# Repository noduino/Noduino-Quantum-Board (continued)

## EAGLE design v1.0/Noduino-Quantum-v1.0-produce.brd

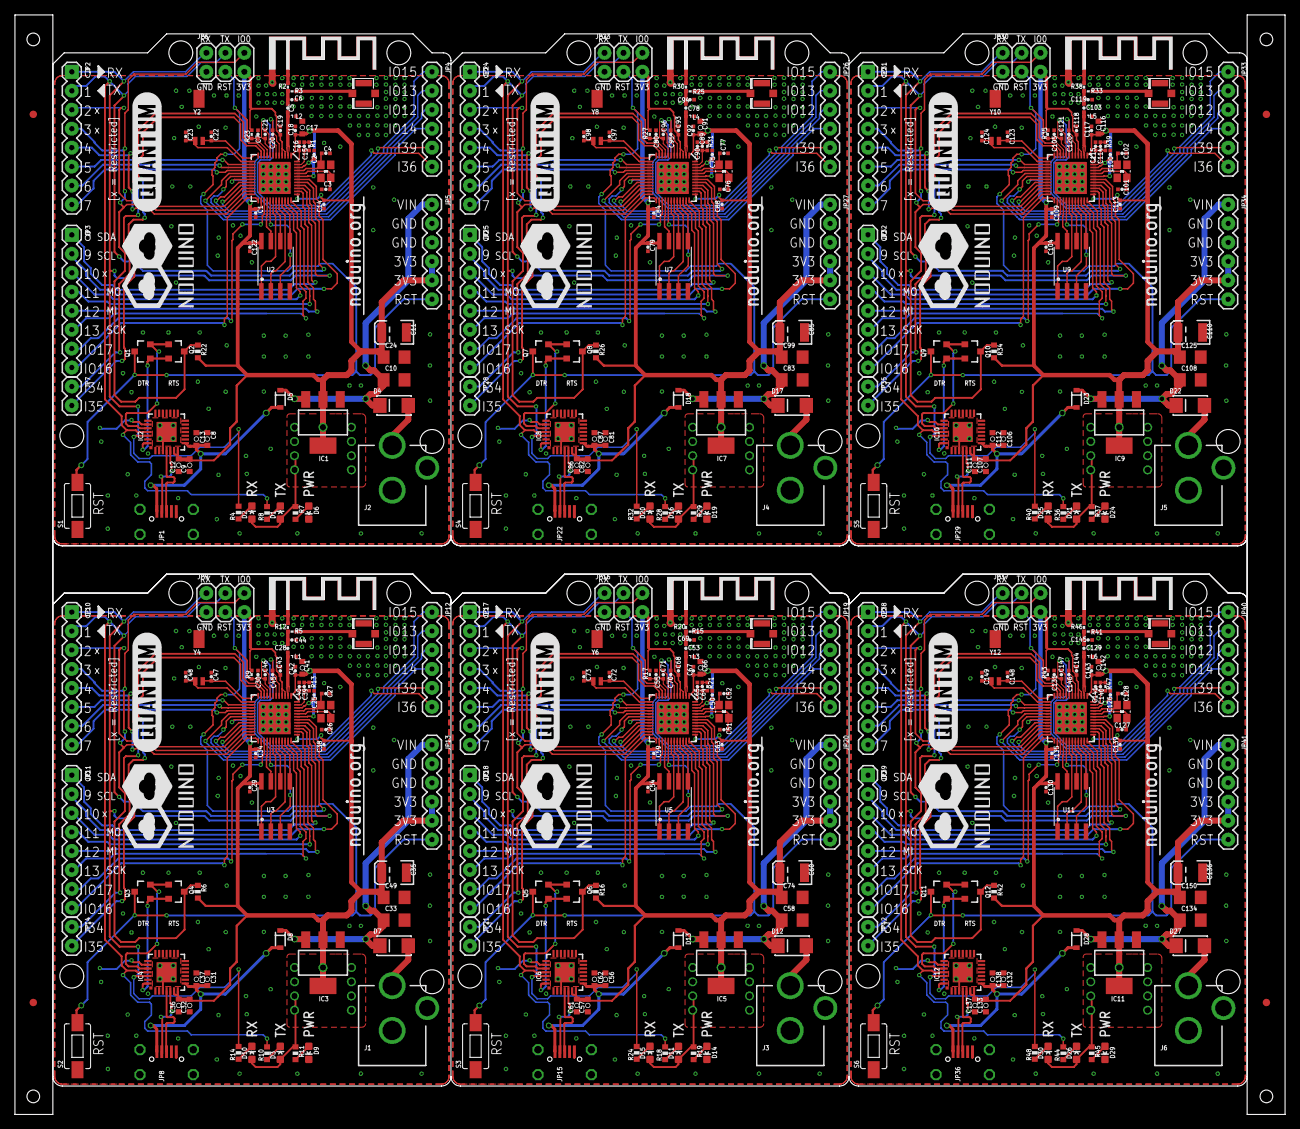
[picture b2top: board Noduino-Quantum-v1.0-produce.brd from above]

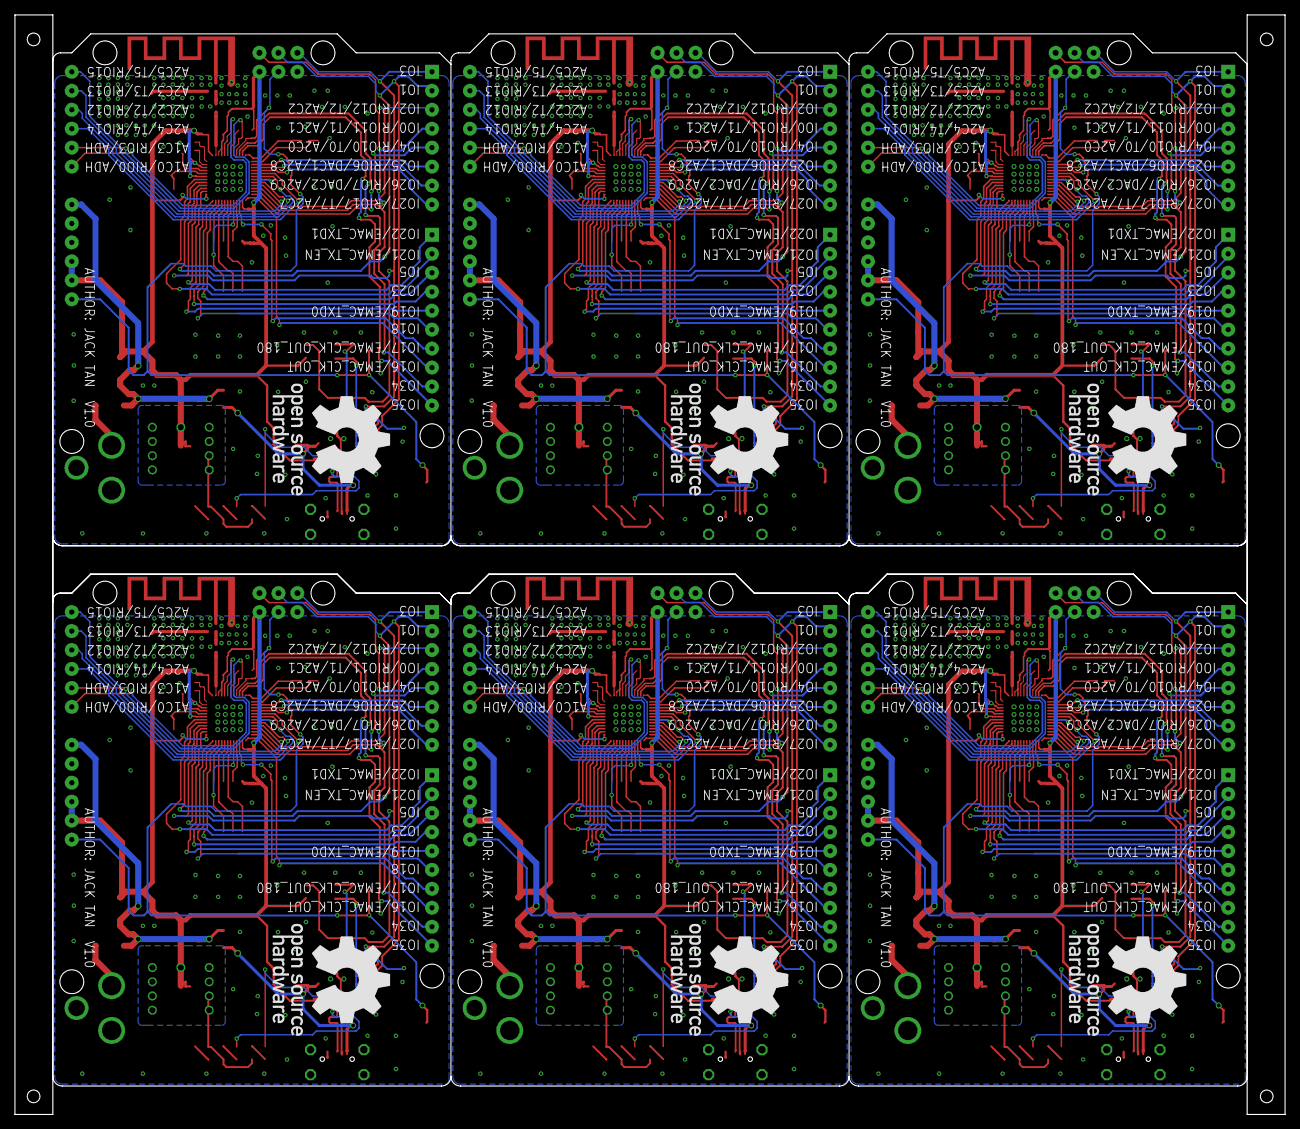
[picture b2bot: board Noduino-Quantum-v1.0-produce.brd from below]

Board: 2 copper layers, 170.2 x 147.3 mm, 370 parts (6 on the bottom side), 330 nets.

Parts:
A1, A4, A6, A8, A10, A12: TRACE_ANTENNA_2.4GHZ_15.2MM_TPLACE
A2, A3, A5, A7, A9, A11: U.FL
C1, C7, C14, C18, C19, C29, C30, C34, C38, C42, C43, C54, C55, C59, C63, C67, C68, C79, C80, C84, C88, C92, C93, C104, C105, C109, C113, C117, C118, C122, C130, C131, C135, C139, C143, C144: 100nF; 0402-CAP
C2, C25, C50, C75, C100, C126: 100pF; 0402-CAP
C3, C4, C26, C27, C51, C52, C76, C77, C101, C102, C127, C128: 15pF; 0402-CAP
C5, C28, C53, C78, C103, C129: 6.8pF; 0402-CAP
C6, C44, C69, C94, C119, C145: 2.4pF; 0402-CAP
C8, C9, C31, C32, C56, C57, C81, C82, C106, C107, C132, C133: 100nF; 0603-CAP
C10, C33, C58, C83, C108, C134: 22uF; C1206
C11, C35, C60, C85, C110, C136: 100uF; EIA3528
C12, C36, C61, C86, C111, C137: 4.7uF; 0603-CAP
C13, C37, C62, C87, C112, C138: 1uF; 0603-CAP
C15, C39, C64, C89, C114, C140: 3nF; 0402-CAP
C16, C40, C65, C90, C115, C141: 10nF; 0402-CAP
C17, C41, C66, C91, C116, C142: 10uF; 0603-CAP
C20, C21, C45, C46, C70, C71, C95, C96, C120, C121, C146, C147: 270pF; 0402-CAP
C22, C23, C47, C48, C72, C73, C97, C98, C123, C124, C148, C149: 12pF; 0402-CAP
C24, C49, C74, C99, C125, C150: 10uF; C1206
D1, D2, D3, D10, D11, D15, D16, D20, D21, D25, D26, D30: BLUE; LED-0603
D4, D7, D12, D17, D22, D27: SS4; DO214
D5, D8, D13, D18, D23, D28: S4; SOD-323
D6, D9, D14, D19, D24, D29: GREEN; LED-0603
E$1, E$2, E$3, E$4: MARK-1MM
IC1, IC3, IC5, IC7, IC9, IC11: 1117-3.3; SOT223
IC2, IC4, IC6, IC8, IC10, IC12: CP210X_USB_UART; MLP28
J1, J2, J3, J4, J5, J6: POWER_JACKPTH; POWER_JACK_PTH
JP1, JP8, JP15, JP22, JP29, JP36: MICROUSB-SMD-DIP
JP2, JP3, JP10, JP11, JP17, JP18, JP24, JP25, JP31, JP32, JP38, JP39: M081X08; 1X08
JP4, JP5, JP12, JP13, JP19, JP20, JP26, JP27, JP33, JP34, JP40, JP41: M06SIP; 1X06
JP6, JP9, JP16, JP23, JP30, JP37: M02X3; 2X3
JP7, JP14, JP21, JP28, JP35, JP42: 1X02
L1, L2, L3, L4, L5, L6: 1.6nH; 0402-IND
Q1, Q2, Q3, Q4, Q5, Q6, Q7, Q8, Q9, Q10, Q11, Q12: SI2302; SOT23-3
R1, R13, R21, R31, R39, R47: 20K; 0402-RES
R2, R12, R20, R30, R38, R46: 0R; 0402-RES
R3, R5, R15, R25, R33, R41: DNP; 0402-RES
R4, R7, R8, R10, R11, R14, R18, R19, R24, R28, R29, R32, R36, R37, R40, R44, R45, R48: 1K; 0603-RES
R6, R16, R22, R26, R34, R42: 10K; 0603-RES
R9, R17, R23, R27, R35, R43: 10K; 0402-RES
S1, S2, S3, S4, S5, S6: SWITCH-SMD; TACTILE-SWITCH-1101NE
U1, U4, U6, U8, U10, U12: ESP32; QFN48-0.4MM
U2, U3, U5, U7, U9, U11: SPI_FLASH-X25XXSMD1; SO08-EIAJ
U$1, U$4, U$7, U$10, U$13, U$16: NODUINO-LOGO-ALL; NODUINO-ALL-1
U$2, U$5, U$8, U$11, U$14, U$17: NODUINO-QUANTUM-LOGO
U$3, U$6, U$9, U$12, U$15, U$18: OPEN_HARDWARE_LOGO
Y1, Y3, Y5, Y7, Y9, Y11: 40MHz; 2520-CRY
Y2, Y4, Y6, Y8, Y10, Y12: 32KHz; CRYSTAL-32KHZ-MS3V

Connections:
3V1: C25.1, C29.1, C32.2, C34.1, C35.A, C36.2, C38.2, C41.1, C42.1, C43.2, C49.1, D3.A, D10.A, IC3.2, IC3.4, IC4.6, IC4.7, JP9.5, JP13.4, JP13.5, R6.2, R9.2, R11.1, U3.8, U4.1, U4.3, U4.4, U4.19, U4.26, U4.37, U4.43, U4.46
3V2: C50.1, C54.1, C57.2, C59.1, C60.A, C61.2, C63.2, C66.1, C67.1, C68.2, C74.1, D11.A, D15.A, IC5.2, IC5.4, IC6.6, IC6.7, JP16.5, JP20.4, JP20.5, R16.2, R17.2, R19.1, U5.8, U6.1, U6.3, U6.4, U6.19, U6.26, U6.37, U6.43, U6.46
3V3: C1.1, C2.1, C9.2, C11.A, C12.2, C14.2, C17.1, C18.1, C19.2, C24.1, C122.1, D1.A, D2.A, IC1.2, IC1.4, IC2.6, IC2.7, JP5.4, JP5.5, JP6.5, R7.1, R22.2, R23.2, U1.1, U1.3, U1.4, U1.19, U1.26, U1.37, U1.43, U1.46, U2.8
3V4: C75.1, C79.1, C82.2, C84.1, C85.A, C86.2, C88.2, C91.1, C92.1, C93.2, C99.1, D16.A, D20.A, IC7.2, IC7.4, IC8.6, IC8.7, JP23.5, JP27.4, JP27.5, R26.2, R27.2, R29.1, U7.8, U8.1, U8.3, U8.4, U8.19, U8.26, U8.37, U8.43, U8.46
3V5: C100.1, C104.1, C107.2, C109.1, C110.A, C111.2, C113.2, C116.1, C117.1, C118.2, C125.1, D21.A, D25.A, IC9.2, IC9.4, IC10.6, IC10.7, JP30.5, JP34.4, JP34.5, R34.2, R35.2, R37.1, U9.8, U10.1, U10.3, U10.4, U10.19, U10.26, U10.37, U10.43, U10.46
3V6: C126.1, C130.1, C133.2, C135.1, C136.A, C137.2, C139.2, C142.1, C143.1, C144.2, C150.1, D26.A, D30.A, IC11.2, IC11.4, IC12.6, IC12.7, JP37.5, JP41.4, JP41.5, R42.2, R43.2, R45.1, U11.8, U12.1, U12.3, U12.4, U12.19, U12.26, U12.37, U12.43, U12.46
DTR: IC2.28, Q1.1, Q2.2
DTR1: IC4.28, Q3.1, Q4.2
DTR2: IC6.28, Q5.1, Q6.2
DTR3: IC8.28, Q7.1, Q8.2
DTR4: IC10.28, Q9.1, Q10.2
DTR5: IC12.28, Q11.1, Q12.2
GND: A1.GND, A2.P$1, A2.P$2, C1.2, C2.2, C3.1, C4.2, C6.2, C7.2, C8.1, C9.1, C10.2, C11.C, C12.1, C13.1, C14.1, C16.2, C17.2, C18.2, C19.1, C22.1, C23.1, C24.2, C122.2, D6.C, IC1.1, IC2.3, IC2.EXP, IC2.M, J2.GND, J2.GNDBREAK, JP1.GND1, JP1.P$1, JP1.P$2, JP1.P$3, JP1.P$4, JP5.2, JP5.3, JP6.1, L2.1, S1.P$1, U1.EP, U2.4, Y1.2, Y1.4
GND1: A3.P$1, A3.P$2, A4.GND, C25.2, C26.1, C27.2, C29.2, C30.2, C31.1, C32.1, C33.2, C34.2, C35.C, C36.1, C37.1, C38.1, C40.2, C41.2, C42.2, C43.1, C44.2, C47.1, C48.1, C49.2, D9.C, IC3.1, IC4.3, IC4.EXP, IC4.M, J1.GND, J1.GNDBREAK, JP8.GND1, JP8.P$1, JP8.P$2, JP8.P$3, JP8.P$4, JP9.1, JP13.2, JP13.3, L1.1, S2.P$1, U3.4, U4.EP, Y3.2, Y3.4
GND2: A5.P$1, A5.P$2, A6.GND, C50.2, C51.1, C52.2, C54.2, C55.2, C56.1, C57.1, C58.2, C59.2, C60.C, C61.1, C62.1, C63.1, C65.2, C66.2, C67.2, C68.1, C69.2, C72.1, C73.1, C74.2, D14.C, IC5.1, IC6.3, IC6.EXP, IC6.M, J3.GND, J3.GNDBREAK, JP15.GND1, JP15.P$1, JP15.P$2, JP15.P$3, JP15.P$4, JP16.1, JP20.2, JP20.3, L3.1, S3.P$1, U5.4, U6.EP, Y5.2, Y5.4
GND3: A7.P$1, A7.P$2, A8.GND, C75.2, C76.1, C77.2, C79.2, C80.2, C81.1, C82.1, C83.2, C84.2, C85.C, C86.1, C87.1, C88.1, C90.2, C91.2, C92.2, C93.1, C94.2, C97.1, C98.1, C99.2, D19.C, IC7.1, IC8.3, IC8.EXP, IC8.M, J4.GND, J4.GNDBREAK, JP22.GND1, JP22.P$1, JP22.P$2, JP22.P$3, JP22.P$4, JP23.1, JP27.2, JP27.3, L4.1, S4.P$1, U7.4, U8.EP, Y7.2, Y7.4
GND4: A9.P$1, A9.P$2, A10.GND, C100.2, C101.1, C102.2, C104.2, C105.2, C106.1, C107.1, C108.2, C109.2, C110.C, C111.1, C112.1, C113.1, C115.2, C116.2, C117.2, C118.1, C119.2, C123.1, C124.1, C125.2, D24.C, IC9.1, IC10.3, IC10.EXP, IC10.M, J5.GND, J5.GNDBREAK, JP29.GND1, JP29.P$1, JP29.P$2, JP29.P$3, JP29.P$4, JP30.1, JP34.2, JP34.3, L5.1, S5.P$1, U9.4, U10.EP, Y9.2, Y9.4
GND5: A11.P$1, A11.P$2, A12.GND, C126.2, C127.1, C128.2, C130.2, C131.2, C132.1, C133.1, C134.2, C135.2, C136.C, C137.1, C138.1, C139.1, C141.2, C142.2, C143.2, C144.1, C145.2, C148.1, C149.1, C150.2, D29.C, IC11.1, IC12.3, IC12.EXP, IC12.M, J6.GND, J6.GNDBREAK, JP36.GND1, JP36.P$1, JP36.P$2, JP36.P$3, JP36.P$4, JP37.1, JP41.2, JP41.3, L6.1, S6.P$1, U11.4, U12.EP, Y11.2, Y11.4
IO0: JP2.4, JP6.6, Q2.3, R22.1, U1.23
IO1: C46.2, JP12.5, U4.8
IO2: JP2.3, U1.22
IO3: JP11.2, U4.42
IO4: JP2.5, U1.24
IO5: JP3.3, U1.34
IO6: JP11.1, U4.39
IO7: JP11.5, U4.38
IO8: JP14.1, U4.10
IO9: JP14.2, U4.11
IO10: JP10.6, U4.14
IO11: JP10.7, U4.15
IO12: JP4.3, U1.18
IO13: JP4.2, U1.20
IO14: JP4.4, U1.17
IO15: JP4.1, U1.21
IO16: JP3.8, U1.25
IO17: JP3.7, U1.27
IO18: JP3.6, U1.35
IO19: JP3.5, U1.38
IO20: JP10.8, U4.16
IO21: JP3.2, U1.42
IO22: JP3.1, U1.39
IO23: JP3.4, U1.36
IO24: JP10.3, U4.22
IO25: JP2.6, U1.14
IO26: JP2.7, U1.15
IO27: JP2.8, U1.16
IO28: JP12.4, U4.17
IO29: JP12.3, U4.18
IO30: JP12.2, U4.20
IO31: JP12.1, U4.21
IO32: JP9.6, JP10.4, Q4.3, R6.1, U4.23
IO33: JP10.5, U4.24
IO34: JP7.1, U1.10
IO35: JP7.2, U1.11
IO36: C20.1, JP4.6, U1.5
IO37: JP11.8, U4.25
IO38: JP11.7, U4.27
IO39: C21.2, JP4.5, U1.8
IO40: JP11.3, U4.34
IO41: JP11.6, U4.35
IO42: JP11.4, U4.36
IO43: C45.1, JP12.6, U4.5
IO44: C71.2, JP19.5, U6.8
IO45: JP18.2, U6.42
IO46: JP18.1, U6.39
IO47: JP18.5, U6.38
IO48: JP21.1, U6.10
IO49: JP21.2, U6.11
IO50: JP17.6, U6.14
IO51: JP17.7, U6.15
IO52: JP17.8, U6.16
IO53: JP17.3, U6.22
IO54: JP19.4, U6.17
IO55: JP19.3, U6.18
IO56: JP19.2, U6.20
IO57: JP19.1, U6.21
IO58: JP16.6, JP17.4, Q6.3, R16.1, U6.23
IO59: JP17.5, U6.24
IO60: JP18.8, U6.25
IO61: JP18.7, U6.27
IO62: JP18.3, U6.34
IO63: JP18.6, U6.35
IO64: JP18.4, U6.36
IO65: C70.1, JP19.6, U6.5
IO66: C96.2, JP26.5, U8.8
IO67: JP25.2, U8.42
IO68: JP25.1, U8.39
IO69: JP25.5, U8.38
IO70: JP28.1, U8.10
IO71: JP28.2, U8.11
IO72: JP24.6, U8.14
IO73: JP24.7, U8.15
IO74: JP24.8, U8.16
IO75: JP24.3, U8.22
IO76: JP26.4, U8.17
IO77: JP26.3, U8.18
IO78: JP26.2, U8.20
IO79: JP26.1, U8.21
IO80: JP23.6, JP24.4, Q8.3, R26.1, U8.23
IO81: JP24.5, U8.24
IO82: JP25.8, U8.25
IO83: JP25.7, U8.27
IO84: JP25.3, U8.34
IO85: JP25.6, U8.35
IO86: JP25.4, U8.36
IO87: C95.1, JP26.6, U8.5
IO88: C121.2, JP33.5, U10.8
IO89: JP32.2, U10.42
IO90: JP32.1, U10.39
IO91: JP32.5, U10.38
IO92: JP35.1, U10.10
IO93: JP35.2, U10.11
IO94: JP31.6, U10.14
IO95: JP31.7, U10.15
IO96: JP31.8, U10.16
IO97: JP31.3, U10.22
IO98: JP33.4, U10.17
IO99: JP33.3, U10.18
IO100: JP33.2, U10.20
IO101: JP33.1, U10.21
IO102: JP30.6, JP31.4, Q10.3, R34.1, U10.23
IO103: JP31.5, U10.24
IO104: JP32.8, U10.25
IO105: JP32.7, U10.27
IO106: JP32.3, U10.34
IO107: JP32.6, U10.35
IO108: JP32.4, U10.36
IO109: C120.1, JP33.6, U10.5
IO110: C147.2, JP40.5, U12.8
IO111: JP39.2, U12.42
IO112: JP39.1, U12.39
IO113: JP39.5, U12.38
IO114: JP42.1, U12.10
IO115: JP42.2, U12.11
IO116: JP38.6, U12.14
IO117: JP38.7, U12.15
IO118: JP38.8, U12.16
IO119: JP38.3, U12.22
IO120: JP40.4, U12.17
IO121: JP40.3, U12.18
IO122: JP40.2, U12.20
IO123: JP40.1, U12.21
IO124: JP37.6, JP38.4, Q12.3, R42.1, U12.23
IO125: JP38.5, U12.24
IO126: JP39.8, U12.25
IO127: JP39.7, U12.27
IO128: JP39.3, U12.34
IO129: JP39.6, U12.35
IO130: JP39.4, U12.36
IO131: C146.1, JP40.6, U12.5
LNA: C5.2, L2.2, U1.2
LNA1: C28.2, L1.2, U4.2
LNA2: C53.2, L3.2, U6.2
LNA3: C78.2, L4.2, U8.2
LNA4: C103.2, L5.2, U10.2
LNA5: C129.2, L6.2, U12.2
unnamed: D1.C, R8.1
unnamed: C4.1, U1.45, Y1.3
unnamed: C3.2, U1.44, Y1.1
unnamed: IC2.4, JP1.D+1
unnamed: A1.ANT, R2.1
unnamed: C27.1, U4.45, Y3.3
unnamed: IC2.5, JP1.D-1
unnamed: C26.2, U4.44, Y3.1
unnamed: C15.2, R1.2, U1.47
unnamed: D2.C, R4.1
unnamed: D6.A, R7.2
unnamed: C28.1, C44.1, R5.1
unnamed: D3.C, R10.1
unnamed: D4.A, J2.PWR
unnamed: C15.1, C16.1, R1.1, U1.48
unnamed: A2.P$3, R3.2
unnamed: IC4.4, JP8.D+1
unnamed: C5.1, C6.1, R3.1
unnamed: D9.A, R11.2
unnamed: A4.ANT, R12.1
unnamed: D7.A, J1.PWR
unnamed: C21.1, U1.7
unnamed: A3.P$3, R5.2
unnamed: C20.2, U1.6
unnamed: IC4.5, JP8.D-1
unnamed: C22.2, U1.12, Y2.P$2
unnamed: C23.2, U1.13, Y2.P$1
unnamed: C39.2, R13.2, U4.47
unnamed: C39.1, C40.1, R13.1, U4.48
unnamed: C46.1, U4.7
unnamed: C45.2, U4.6
unnamed: C47.2, U4.12, Y4.P$2
unnamed: C48.2, U4.13, Y4.P$1
unnamed: D10.C, R14.1
unnamed: C52.1, U6.45, Y5.3
unnamed: C51.2, U6.44, Y5.1
unnamed: C53.1, C69.1, R15.1
unnamed: D11.C, R18.1
unnamed: IC6.4, JP15.D+1
unnamed: D14.A, R19.2
unnamed: A6.ANT, R20.1
unnamed: D12.A, J3.PWR
unnamed: A5.P$3, R15.2
unnamed: IC6.5, JP15.D-1
unnamed: C64.2, R21.2, U6.47
unnamed: C64.1, C65.1, R21.1, U6.48
unnamed: C71.1, U6.7
unnamed: C70.2, U6.6
unnamed: C72.2, U6.12, Y6.P$2
unnamed: C73.2, U6.13, Y6.P$1
unnamed: D15.C, R24.1
unnamed: C77.1, U8.45, Y7.3
unnamed: C76.2, U8.44, Y7.1
unnamed: C78.1, C94.1, R25.1
unnamed: D16.C, R28.1
unnamed: IC8.4, JP22.D+1
unnamed: D19.A, R29.2
unnamed: A8.ANT, R30.1
unnamed: D17.A, J4.PWR
unnamed: A7.P$3, R25.2
unnamed: IC8.5, JP22.D-1
unnamed: C89.2, R31.2, U8.47
unnamed: C89.1, C90.1, R31.1, U8.48
unnamed: C96.1, U8.7
unnamed: C95.2, U8.6
unnamed: C97.2, U8.12, Y8.P$2
unnamed: C98.2, U8.13, Y8.P$1
unnamed: D20.C, R32.1
unnamed: C102.1, U10.45, Y9.3
unnamed: C101.2, U10.44, Y9.1
unnamed: C103.1, C119.1, R33.1
unnamed: D21.C, R36.1
unnamed: IC10.4, JP29.D+1
unnamed: D24.A, R37.2
unnamed: A10.ANT, R38.1
unnamed: D22.A, J5.PWR
unnamed: A9.P$3, R33.2
unnamed: IC10.5, JP29.D-1
unnamed: C114.2, R39.2, U10.47
unnamed: C114.1, C115.1, R39.1, U10.48
unnamed: C121.1, U10.7
unnamed: C120.2, U10.6
unnamed: C123.2, U10.12, Y10.P$2
unnamed: C124.2, U10.13, Y10.P$1
unnamed: D25.C, R40.1
unnamed: C128.1, U12.45, Y11.3
unnamed: C127.2, U12.44, Y11.1
unnamed: C129.1, C145.1, R41.1
unnamed: D26.C, R44.1
unnamed: IC12.4, JP36.D+1
unnamed: D29.A, R45.2
unnamed: A12.ANT, R46.1
unnamed: D27.A, J6.PWR
unnamed: A11.P$3, R41.2
unnamed: IC12.5, JP36.D-1
unnamed: C140.2, R47.2, U12.47
unnamed: C140.1, C141.1, R47.1, U12.48
unnamed: C147.1, U12.7
unnamed: C146.2, U12.6
unnamed: C148.2, U12.12, Y12.P$2
unnamed: C149.2, U12.13, Y12.P$1
unnamed: D30.C, R48.1
RST: C7.1, JP5.6, JP6.3, Q1.3, R23.1, S1.P$2, U1.9
RST1: C30.1, JP9.3, JP13.6, Q3.3, R9.1, S2.P$2, U4.9
RST2: C55.1, JP16.3, JP20.6, Q5.3, R17.1, S3.P$2, U6.9
RST3: C80.1, JP23.3, JP27.6, Q7.3, R27.1, S4.P$2, U8.9
RST4: C105.1, JP30.3, JP34.6, Q9.3, R35.1, S5.P$2, U10.9
RST5: C131.1, JP37.3, JP41.6, Q11.3, R43.1, S6.P$2, U12.9
RTS: IC2.24, Q1.2, Q2.1
RTS1: IC4.24, Q3.2, Q4.1
RTS2: IC6.24, Q5.2, Q6.1
RTS3: IC8.24, Q7.2, Q8.1
RTS4: IC10.24, Q9.2, Q10.1
RTS5: IC12.24, Q11.2, Q12.1
SD_CLK: U1.31, U2.6
SD_CLK1: U3.6, U4.31
SD_CLK2: U5.6, U6.31
SD_CLK3: U7.6, U8.31
SD_CLK4: U9.6, U10.31
SD_CLK5: U11.6, U12.31
SD_CMD: U1.30, U2.1
SD_CMD1: U3.1, U4.30
SD_CMD2: U5.1, U6.30
SD_CMD3: U7.1, U8.30
SD_CMD4: U9.1, U10.30
SD_CMD5: U11.1, U12.30
SD_D0: U1.32, U2.2
SD_D1: U1.33, U2.5
SD_D2: U1.28, U2.7
SD_D3: U1.29, U2.3
SD_D4: U3.3, U4.29
SD_D5: U3.7, U4.28
SD_D6: U3.5, U4.33
SD_D7: U3.2, U4.32
SD_D8: U5.3, U6.29
SD_D9: U5.7, U6.28
SD_D10: U5.5, U6.33
SD_D11: U5.2, U6.32
SD_D12: U7.3, U8.29
SD_D13: U7.7, U8.28
SD_D14: U7.5, U8.33
SD_D15: U7.2, U8.32
SD_D16: U9.3, U10.29
SD_D17: U9.7, U10.28
SD_D18: U9.5, U10.33
SD_D19: U9.2, U10.32
SD_D20: U11.3, U12.29
SD_D21: U11.7, U12.28
SD_D22: U11.5, U12.33
SD_D23: U11.2, U12.32
U0RX: IC2.26, JP2.1, JP6.2, R4.2, U1.40
U0RX1: IC4.26, JP9.2, JP10.1, R14.2, U4.40
U0RX2: IC6.26, JP16.2, JP17.1, R24.2, U6.40
U0RX3: IC8.26, JP23.2, JP24.1, R32.2, U8.40
U0RX4: IC10.26, JP30.2, JP31.1, R40.2, U10.40
U0RX5: IC12.26, JP37.2, JP38.1, R48.2, U12.40
U0TX: IC2.25, JP2.2, JP6.4, R8.2, U1.41
U0TX1: IC4.25, JP9.4, JP10.2, R10.2, U4.41
U0TX2: IC6.25, JP16.4, JP17.2, R18.2, U6.41
U0TX3: IC8.25, JP23.4, JP24.2, R28.2, U8.41
U0TX4: IC10.25, JP30.4, JP31.2, R36.2, U10.41
U0TX5: IC12.25, JP37.4, JP38.2, R44.2, U12.41
USBVCC: C8.2, C13.2, D5.2, IC2.8, JP1.VBUS1
USBVCC1: C31.2, C37.2, D8.2, IC4.8, JP8.VBUS1
USBVCC2: C56.2, C62.2, D13.2, IC6.8, JP15.VBUS1
USBVCC3: C81.2, C87.2, D18.2, IC8.8, JP22.VBUS1
USBVCC4: C106.2, C112.2, D23.2, IC10.8, JP29.VBUS1
USBVCC5: C132.2, C138.2, D28.2, IC12.8, JP36.VBUS1
VIN: C10.1, D4.C, D5.1, IC1.3, JP5.1
VIN1: C33.1, D7.C, D8.1, IC3.3, JP13.1
VIN2: C58.1, D12.C, D13.1, IC5.3, JP20.1
VIN3: C83.1, D17.C, D18.1, IC7.3, JP27.1
VIN4: C108.1, D22.C, D23.1, IC9.3, JP34.1
VIN5: C134.1, D27.C, D28.1, IC11.3, JP41.1

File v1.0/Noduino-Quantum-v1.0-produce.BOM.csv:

Partlist for Project:                                                  ,,,,,,,,
Customer:                                                              ,,,,,,,,
File:  c:/users/jack/documents/eagle/noduino/quantum/v1.0/noduino-quantum-v1.0-produce.brd.bom,,,,,,,,
"Prepared by:  Group #____  SFU Engineering Science, ENSC 204    2016/11/16 16:11:59 ",,,,,,,,
,,,,,,,,
Item,Qty,Part Number,Description,Package,Manufacturer,Suggested Suppliers,Sub/Comments,Part ID.
5,6,2.4pF, ,0402-CAP, , , ,"C6,C44,C69,C94,C119,C145"
6,6,3nF, ,0402-CAP, , , ,"C15,C39,C64,C89,C114,C140"
7,6,6.8pF, ,0402-CAP, , , ,"C5,C28,C53,C78,C103,C129"
8,6,10nF, ,0402-CAP, , , ,"C16,C40,C65,C90,C115,C141"
9,12,12pF, ,0402-CAP, , , ,"C22,C23,C47,C48,C72,C73,C97,C98,C123,C124,C148,C149"
10,12,15pF, ,0402-CAP, , , ,"C3,C4,C26,C27,C51,C52,C76,C77,C101,C102,C127,C128"
11,48,100nF, ,0402-CAP, , , ,"C1,C7,C14,C18,C19,C29,C30,C34,C38,C42,C43,C54,C55,C59,C63,C67,C68,C79,C80,C84,C88,C92,C93,C104,C105,C109,C113,C117,C118,C122,C130,C131,C135,C139,C143,C144,C8,C9,C31,C32,C56,C57,C81,C82,C106,C107,C132,C133"
12,6,100pF, ,0402-CAP, , , ,"C2,C25,C50,C75,C100,C126"
13,12,270pF, ,0402-CAP, , , ,"C20,C21,C45,C46,C70,C71,C95,C96,C120,C121,C146,C147"
14,6,1.6nH, ,0402-IND, , , ,"L1,L2,L3,L4,L5,L6"
15,6,0R, ,0402-RES, , , ,"R2,R12,R20,R30,R38,R46"
16,12,10K, ,0402-RES, , , ,"R9,R17,R23,R27,R35,R43,R6,R16,R22,R26,R34,R42"
17,6,20K, ,0402-RES, , , ,"R1,R13,R21,R31,R39,R47"
18,6,DNP£¬´ËÆ÷¼þ²»ÓÃÌù, ,0402-RES, , , ,"R3,R5,R15,R25,R33,R41"
19,6,1uF, ,0603-CAP, , , ,"C13,C37,C62,C87,C112,C138"
20,6,4.7uF, ,0603-CAP, , , ,"C12,C36,C61,C86,C111,C137"
21,6,10uF, ,0603-CAP, , , ,"C17,C41,C66,C91,C116,C142"
22,18,1K, ,0603-RES, , , ,"R4,R7,R8,R10,R11,R14,R18,R19,R24,R28,R29,R32,R36,R37,R40,R44,R45,R48"
23,6,40MHz, ,2520-CRY, , , ,"Y1,Y3,Y5,Y7,Y9,Y11"
24,6,10uF, ,C1206, , , ,"C24,C49,C74,C99,C125,C150"
25,6,10uF, ,C1206, , , ,"C10,C33,C58,C83,C108,C134"
26,6,32KHz, ,CRYSTAL-32KHZ-MS3V, , , ,"Y2,Y4,Y6,Y8,Y10,Y12"
27,6,M7, ,DO214, , , ,"D4,D7,D12,D17,D22,D27"
28,6,100uF, ,EIA3528, , , ,"C11,C35,C60,C85,C110,C136"
29,12,GREEN-LED ÂÌÉ«LED, ,LED-0603, , , ,"D1,D2,D3,D10,D11,D15,D16,D20,D21,D25,D26,D30"
30,6,BLUE-LED À¶É«LED, ,LED-0603, , , ,"D6,D9,D14,D19,D24,D29"
31,6,CP2102, ,MLP28, , , ,"IC2,IC4,IC6,IC8,IC10,IC12"
35,6,POWER_JACKPTH, ,POWER_JACK_PTH, , , ,"J1,J2,J3,J4,J5,J6"
36,6,ESP32, ,QFN48-0.4MM, , , ,"U1,U4,U6,U8,U10,U12"
37,6,W25Q128FVT, ,SO08-EIAJ, , , ,"U2,U3,U5,U7,U9,U11"
38,6,s4, ,SOD-323, , , ,"D5,D8,D13,D18,D23,D28"
39,12,DTC143ECA, ,SOT23-3, , , ,"Q1,Q2,Q3,Q4,Q5,Q6,Q7,Q8,Q9,Q10,Q11,Q12"
40,6,1117-3.3, ,SOT223, , , ,"IC1,IC3,IC5,IC7,IC9,IC11"
41,6,SWITCH-SMD, ,TACTILE-SWITCH-1101NE, , , ,"S1,S2,S3,S4,S5,S6"
42,6,IPX, ,IPX, , , ,"A2,A3,A5,A7,A9,A11"

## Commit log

2017-09-28 add the gerber files of v0.8
2017-09-28 add the sch and brd files of v0.8
2019-05-14 add the new version 1.0
    Including the produce files
